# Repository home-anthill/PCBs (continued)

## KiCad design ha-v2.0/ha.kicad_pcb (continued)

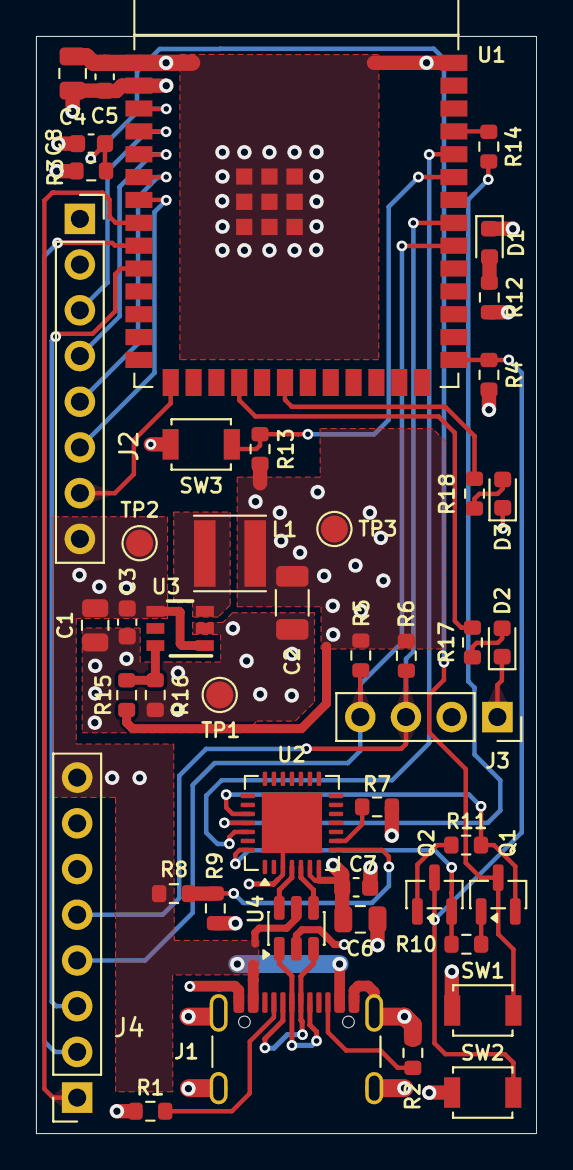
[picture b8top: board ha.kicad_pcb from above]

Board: 4 copper layers, 27.8 x 61.0 mm, 46 parts (0 on the bottom side), 38 nets.

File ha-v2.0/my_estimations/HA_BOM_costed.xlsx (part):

HA BOM — component pricing for 5 assembled boards
Exact-MPN prices are reused from the accepted PCBWay quotation; all other price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
Item # | Reference Designator | Qty / PCB | Qty × 5 | Manufacturer | MPN | Part Description / Value | DigiKey Part Number | Package / Footprint | Type | Assembly Notes | Unit Price (USD) | Cost / PCB (USD) | Cost × 5 (USD) | Price basis | Price source | Source URL
1 | C1,C4 | 2 | 10 | Yageo | CC0805MKX5R6BB106 | 10uF 10V X5R ±20% | 311-1898-1-ND | Capacitor_SMD:C_0805_2012Metric | SMT |  | 0.45200000000000001 | 0.90400000000000003 | 4.5200000000000005 | Preventivo accettato (MPN identico) | Quotation T-1M2W1132271A-5units-HA_BOM(2026-08-19)-FINAL-ACCEPTED.xls
2 | C2 | 1 | 5 | Murata Electronics | GRM31CR61A476ME15L | 47uF, 10V, X5R | 490-5528-1-ND | Capacitor_SMD:C_1206_3216Metric | SMT |  | 0.4 | 0.4 | 2 | DigiKey, prezzo 1 pz | DigiKey, verificato 2026-08-20 | https://www.digikey.it/it/products/detail/murata-electronics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
3 | C3,C5,C7 | 3 | 15 | Yageo | CC0603KRX7R7BB104 | 100nF 16V X7R ±10% | 311-1088-1-ND | Capacitor_SMD:C_0603_1608Metric | SMT |  | 7.1999999999999995E-2 | 0.21599999999999997 | 1.0799999999999998 | Preventivo accettato (MPN identico) | Quotation T-1M2W1132271A-5units-HA_BOM(2026-08-19)-FINAL-ACCEPTED.xls
4 | C6 | 1 | 5 | Yageo | CC0805KKX5R6BB475 | 4.7uF 10V X5R ±10% | 311-1863-1-ND | Capacitor_SMD:C_0805_2012Metric | SMT |  | 0.41599999999999998 | 0.41599999999999998 | 2.08 | Preventivo accettato (MPN identico) | Quotation T-1M2W1132271A-5units-HA_BOM(2026-08-19)-FINAL-ACCEPTED.xls
5 | C8 | 1 | 5 | Yageo | CC0603KRX5R8BB105 | 1uF 25V X5R ±10% | 311-1445-1-ND | Capacitor_SMD:C_0603_1608Metric | SMT |  | 0.14799999999999999 | 0.14799999999999999 | 0.74 | Preventivo accettato (MPN identico) | Quotation T-1M2W1132271A-5units-HA_BOM(2026-08-19)-FINAL-ACCEPTED.xls
6 | D1 | 1 | 5 | Lite-On Inc. | LTST-C190KRKT | LTST-C190KRKT | 160-1436-1-ND | LED_SMD:LED_0603_1608Metric | SMT | Cathode pad 1 toward GND | 0.14000000000000001 | 0.14000000000000001 | 0.70000000000000007 | DigiKey, prezzo 1 pz | DigiKey, verificato 2026-08-20 | https://www.digikey.com/en/products/detail/liteon/LTST-C190K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
7 | J1 | 1 | 5 | GCT | USB4105-GF-A-120 | USB4105-GF-A-120 | 2073-USB4105-GF-A-120CT-ND | Connector_USB:USB_C_Receptacle_GCT_USB4105-xx-A_16P_TopMnt_Horizontal | Hybrid | Top mount; 1.20 mm shell stakes; solder all SH pads; no substitution without ap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 | 1.3280000000000001 | 1.3280000000000001 | 6.6400000000000006 | Preventivo accettato (MPN identico) | Quotation T-1M2W1132271A-5units-HA_BOM(2026-08-19)-FINAL-ACCEPTED.xls
8 | J2 | 1 | 5 | Sullins Connector Solutions | PPTC081LFBN-RC | PPTC081LFBN-RC | S7006-ND | Connector_PinSocket_2.54mm:PinSocket_1x08_P2.54mm_Vertical | THT | THT female socket, vertical, fit on top side; observe pin 1 | 0.57999999999999996 | 0.57999999999999996 | 2.9 | DigiKey, prezzo 1 pz | DigiKey, verificato 2026-08-20 | https://www.digikey.com/en/products/detail/sullins-connector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
9 | J3 | 1 | 5 | Sullins Connector Solutions | PPTC041LFBN-RC | PPTC041LFBN-RC | S3298-ND | Connector_PinSocket_2.54mm:PinSocket_1x04_P2.54mm_Vertical | THT | THT female socket, vertical, fit on top side; observe pin 1 | 0.60899999999999999 | 0.60899999999999999 | 3.0449999999999999 | Preventivo accettato (MPN acquistato identico) | Quotation T-1M2W1132271A-5units-HA_BOM(2026-08-19)-FINAL-ACCEPTED.xls
10 | J4 | 1 | 5 | Sullins Connector Solutions | PPTC071LFBN-RC | PPTC071LFBN-RC | S7005-ND | Connector_PinSocket_2.54mm:PinSocket_1x07_P2.54mm_Vertical | THT | THT female socket, vertical, fit on top side; observe pin 1 | 0.53 | 0.53 | 2.6500000000000004 | DigiKey, prezzo 1 pz | DigiKey, verificato 2026-08-20 | https://www.digikey.com/en/products/detail/sullins-connector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
11 | L1 | 1 | 5 | Taiyo Yuden | MDMK4040T2R2MM | 2.2 µH, Isat=3.8A, Irms=2.8A | 587-4132-1-ND | Inductor_SMD:L_Taiyo-Yuden_MD-4040 | SMT |  | 0.54 | 0.54 | 2.7 | DigiKey, prezzo 1 pz | DigiKey, verificato 2026-08-20 | https://www.digikey.com/en/products/detail/taiyo-yuden/MDMK4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
12 | Q1,Q2 | 2 | 10 | onsemi | MMBT3904LT1G | MMBT3904LT1G | MMBT3904LT1GOSCT-ND | Package_TO_SOT_SMD:SOT-23 | SMT | Pin 1=B, Pin 2=E, Pin 3=C | 0.109 | 0.218 | 1.0900000000000001 | Preventivo accettato (MPN identico) | Quotation T-1M2W1132271A-5units-HA_BOM(2026-08-19)-FINAL-ACCEPTED.xls
13 | R1,R2 | 2 | 10 | Yageo | RC0603FR-075K1L | 5.1k ±1% | 311-5.10KHRCT-ND | Resistor_SMD:R_0603_1608Metric | SMT |  | 3.2000000000000001E-2 | 6.4000000000000001E-2 | 0.32 | Preventivo accettato (MPN identico) | Quotation T-1M2W1132271A-5units-HA_BOM(2026-08-19)-FINAL-ACCEPTED.xls
14 | R3,R4,R10,R11,R13 | 5 | 25 | Yageo | RC0603FR-0710KL | 10k ±1% | 311-10.0KHRCT-ND | Resistor_SMD:R_0603_1608Metric | SMT |  | 2.1000000000000001E-2 | 0.10500000000000001 | 0.52500000000000002 | Preventivo accettato (MPN identico) | Quotation T-1M2W1132271A-5units-HA_BOM(2026-08-19)-FINAL-ACCEPTED.xls
15 | R5,R6 | 2 | 10 | Yageo | RC0603FR-074K7L | 4.7k ±1% | 311-4.70KHRCT-ND | Resistor_SMD:R_0603_1608Metric | SMT |  | 3.2000000000000001E-2 | 6.4000000000000001E-2 | 0.32 | Preventivo accettato (MPN identico) | Quotation T-1M2W1132271A-5units-HA_BOM(2026-08-19)-FINAL-ACCEPTED.xls
16 | R7,R12 | 2 | 10 | Yageo | RC0603FR-071KL | 1k ±1% | 311-1.00KHRCT-ND | Resistor_SMD:R_0603_1608Metric | SMT |  | 3.2000000000000001E-2 | 6.4000000000000001E-2 | 0.32 | Preventivo accettato (MPN identico) | Quotation T-1M2W1132271A-5units-HA_BOM(2026-08-19)-FINAL-ACCEPTED.xls
17 | R8,R16 | 2 | 10 | Yageo | RC0603FR-0722K1L | 22.1k ±1% | 311-22.1KHRCT-ND | Resistor_SMD:R_0603_1608Metric | SMT |  | 5.2999999999999999E-2 | 0.106 | 0.53 | Preventivo accettato (MPN identico) | Quotation T-1M2W1132271A-5units-HA_BOM(2026-08-19)-FINAL-ACCEPTED.xls
18 | R9 | 1 | 5 | Yageo | RC0603FR-0747K5L | 47.5k ±1% | 311-47.5KHRCT-ND | Resistor_SMD:R_0603_1608Metric | SMT |  | 5.2999999999999999E-2 | 5.2999999999999999E-2 | 0.26500000000000001 | Preventivo accettato (MPN identico) | Quotation T-1M2W1132271A-5units-HA_BOM(2026-08-19)-FINAL-ACCEPTED.xls
19 | R14 | 1 | 5 | Yageo | RC0603FR-07499RL | 499R ±1% | 311-499HRCT-ND | Resistor_SMD:R_0603_1608Metric | SMT |  | 5.2999999999999999E-2 | 5.2999999999999999E-2 | 0.26500000000000001 | Preventivo accettato (MPN identico) | Quotation T-1M2W1132271A-5units-HA_BOM(2026-08-19)-FINAL-ACCEPTED.xls
20 | R15 | 1 | 5 | Yageo | RC0603FR-07100KL | 100k ±1% | 311-100KHRCT-ND | Resistor_SMD:R_0603_1608Metric | SMT |  | 0.1 | 0.1 | 0.5 | DigiKey, prezzo 1 pz | DigiKey, verificato 2026-08-20 | https://www.digikey.com/en/products/detail/yageo/RC0603FR-07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
21 | SW1,SW2,SW3 | 3 | 15 | Omron Electronics | B3U-1000P | B3U-1000P | SW1020CT-ND | Button_Switch_SMD:SW_SPST_B3U-1000P | SMT |  | 1.17 | 3.51 | 17.549999999999997 | DigiKey, prezzo 1 pz | DigiKey, verificato 2026-08-20 | https://www.digikey.com/en/products/detail/aratas-formerly-o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
22 | U1 | 1 | 5 | Espressif Systems | ESP32-S3-WROOM-1-N8 | ESP32-S3-WROOM-1-N8 | 5407-ESP32-S3-WROOM-1-N8CT-ND | PCM_Espressif:ESP32-S3-WROOM-1 | SMT | Antenna portion intentionally overhangs PCB edge by 6.0 mm. Maintain panel/rail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 | 4.1260000000000003 | 4.1260000000000003 | 20.630000000000003 | Preventivo accettato (MPN identico) | Quotation T-1M2W1132271A-5units-HA_BOM(2026-08-19)-FINAL-ACCEPTED.xls
23 | U2 | 1 | 5 | Silicon Labs | CP2102N-A02-GQFN28R | CP2102N-A02-GQFN28R | 336-5890-1-ND | Package_DFN_QFN:QFN-28-1EP_5x5mm_P0.5mm_EP3.35x3.35mm | SMT | No substitution without approval | 2.0529999999999999 | 2.0529999999999999 | 10.265000000000001 | Preventivo accettato (MPN identico) | Quotation T-1M2W1132271A-5units-HA_BOM(2026-08-19)-FINAL-ACCEPTED.xls
24 | U3 | 1 | 5 | Texas Instruments | TLV62569PDDCR | TLV62569PDDCR - SOT-23-6 | 296-48175-1-ND | ha-footprints-kicad:DDC0006A_N | SMT |  | 0.27 | 0.27 | 1.35 | DigiKey, prezzo 1 pz | DigiKey, verificato 2026-08-20 | https://www.digikey.com/en/products/detail/texas-instruments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
